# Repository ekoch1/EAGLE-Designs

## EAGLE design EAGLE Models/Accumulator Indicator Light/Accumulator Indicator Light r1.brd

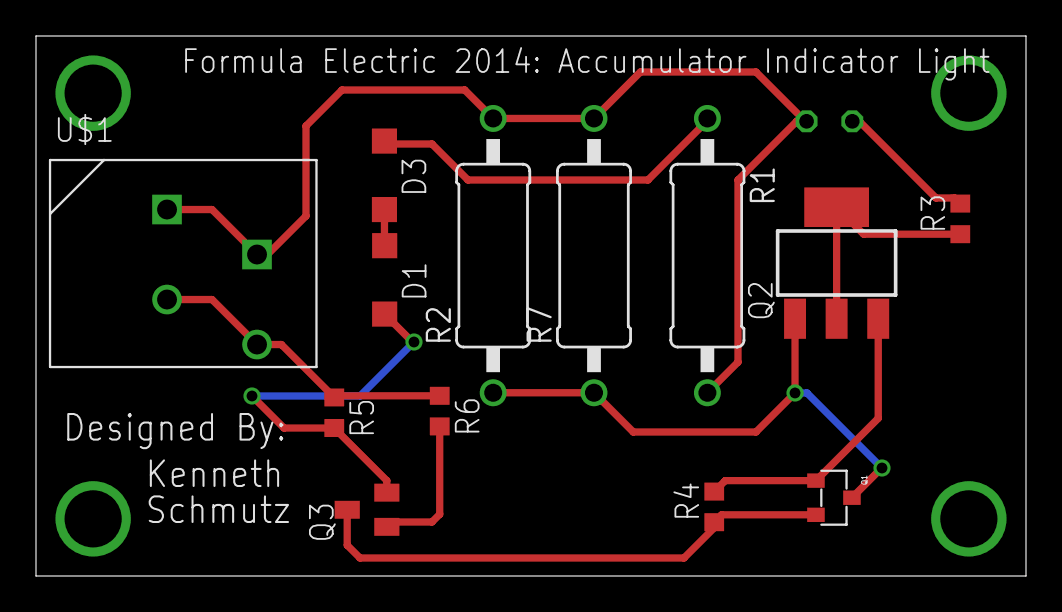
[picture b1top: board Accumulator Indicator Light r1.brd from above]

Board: 2 copper layers, 55.0 x 30.0 mm, 14 parts (1 on the bottom side), 11 nets.

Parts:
D1: DFLZ33; SOD123
D3: BZT52C6V2-7-F; SOD123
LED1: TLLG4400; LED3MM
Q1: MMBT4401-7-F; SOT-23-3
Q2: FZT857; SOT223
Q3: FZT849; SOT23
R1: 100k; 0411/15
R2, R7: 60k; 0411/15
R3: 1k; R0603
R4: 47; R0603
R5: 100k; R0603
R6: 100; R0603
U$1: CONN_2; CONNECTOR_2

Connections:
0: R5.1, R6.1, U$1.3, U$1.4
B1: D1.A, Q3.2, R5.2
B2: Q1.P$1, Q2.1, R2.1, R7.1
C1: Q1.P$3, Q3.3, R4.1
C2: Q2.2, Q2.4, R3.1
E1: Q3.1, R6.2
E2: Q1.P$2, Q2.3, R4.2
unnamed: D1.C, D3.A
unnamed: LED1.K, R3.2
unnamed: LED1.A, R1.2, R2.2, R7.2, U$1.1, U$1.2
R1: D3.C, R1.1

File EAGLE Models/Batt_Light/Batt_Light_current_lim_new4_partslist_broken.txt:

Partlist	exported	from	C:/Users/Kenny	Schmutz/Dropbox/Formula	Electric/Electrical/Models/EAGLE	Models/Batt_Light/Batt_Light_1/Batt_Light_current_lim_new4.sch	at	4/5/2014	4:37:56	PM								
																		
ordered?	Value	Device	Package	Parts	Description	MF	OC_FARNELL	SPICETYPE	SPICE_DESCRIPTION									
yes	100	R-US_R0603	R0603	R6	"RESISTOR,"	American	symbol											
yes	100k	R-US_0411/15	0411/15	R1	"RESISTOR,"	American	symbol											
yes	100k	R-US_R0603	R0603	R5	"RESISTOR,"	American	symbol											
yes	1k	R-US_R0603	R0603	R3	"RESISTOR,"	American	symbol											
have already	2N5210	2N5210	TO92D	Q1	NPN	TRANSISTOR												
yes	30k	R-US_0411/15	0411/15	R2	"RESISTOR,"	American	symbol											
yes	47	R-US_R0603	R0603	R4	"RESISTOR,"	American	symbol											
yes	BZT52C6V2-7-F	ZENER	SOD123	D3	Zener	Diode	diode	Diode										
	CONN_2	CONN_2	CONNECTOR_2	U$1														
yes	DFLZ33	ZENER	SOD123	D1	Zener	Diode	diode	Diode										
	FZT849	NPN	SOT23	Q3	Bipolar	NPN	transistor											
	FZT857	FZT857	SOT223	Q2	FZT857CT-ND													
	TLLG4400	TLLG4400	LED3MM	LED1	Low	Current	(2mA)	LED	3	mm	Tinted	Diffused	Package	color	GREEN	VISHAY	SEMICONDUCTOR	1612435

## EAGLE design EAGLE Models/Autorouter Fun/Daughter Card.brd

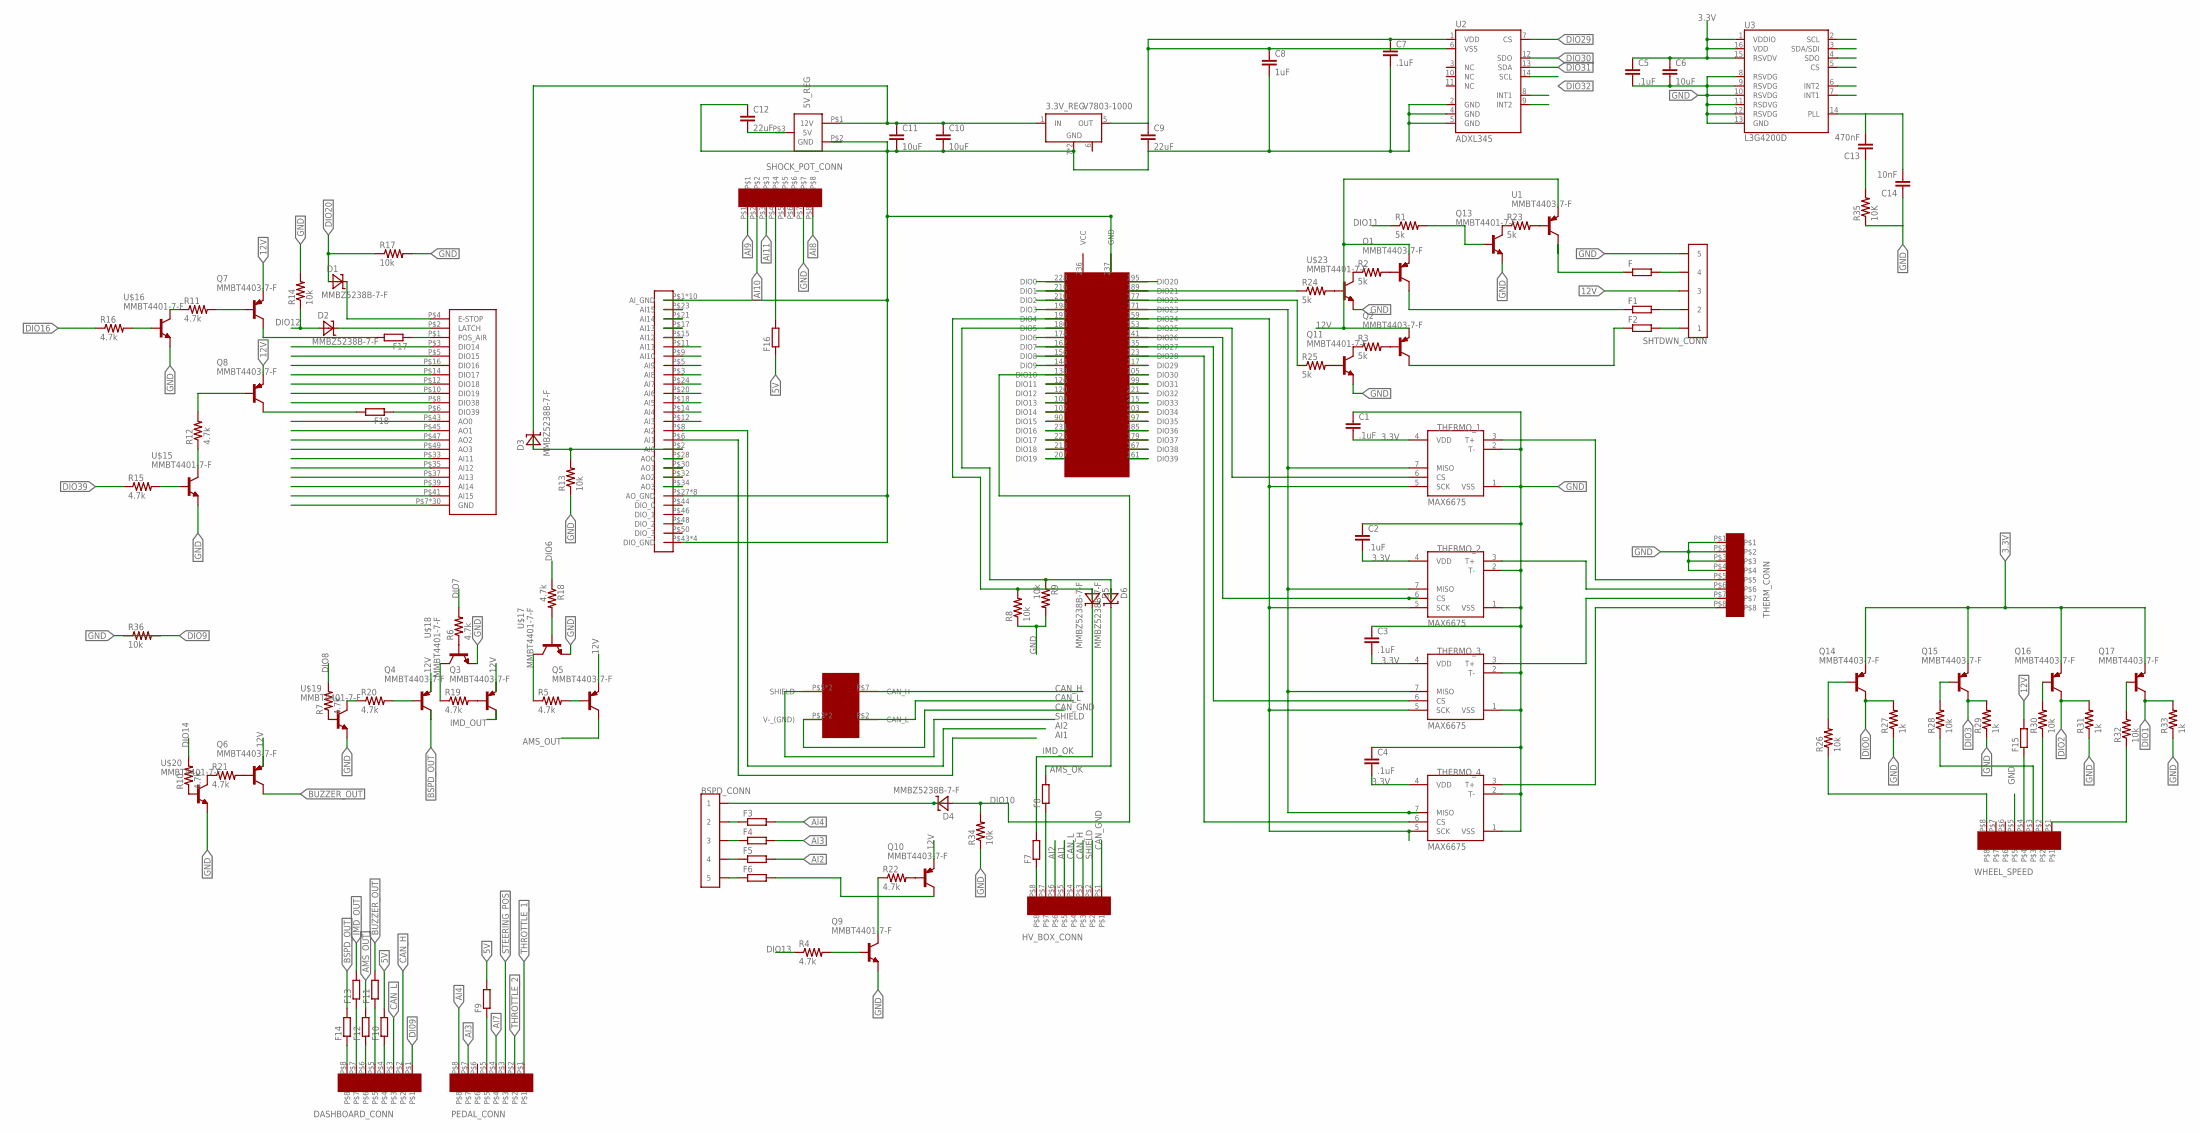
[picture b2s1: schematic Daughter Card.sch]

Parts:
3.3V_REG: V7803-1000; V78XX-1000
5V_REG: V78XX-1500; V78XX-1500R
BSPD_CONN: CONN_5; CONNECTOR_5
C1, C2, C3, C4, C5, C7: .1uF; 0603-CAP
C6, C10, C11: 10uF; 0603-CAP
C8: 1uF; 0603-CAP
C9, C12: 22uF; 0603-CAP
C13: 470nF; 0603-CAP
C14: 10nF; 0603-CAP
D1, D2, D3, D4, D5, D6: MMBZ5238B-7-F; SOT-23-3
DASHBOARD_CONN: EN3_PCB_8
F, F1, F2, F3, F4, F5, F6, F7, F8, F9, F10, F11, F12, F13, F14, F15, F16, F17, F18: R-EU_R0402; R0402
HV_BOX_CONN: EN3_PCB_8
PEDAL_CONN: EN3_PCB_8
Q1, Q2, Q3, Q4, Q5, Q6, Q7, Q8, Q10, Q14, Q15, Q16, Q17: MMBT4403-7-F; SOT-23-3
Q9, Q11, Q13: MMBT4401-7-F; SOT-23-3
R1, R2, R3, R23, R24, R25: 5k; R0402
R4, R5, R6, R7, R10, R11, R12, R15, R16, R18, R19, R20, R21, R22: 4.7k; R0402
R8, R9, R13, R14, R17, R26, R28, R30, R32, R34, R36: 10k; R0402
R27, R29, R31, R33: 1k; R0402
R35: 10K; 0603-RES
SBRIO_ANALOG: SBRIO_MIO; SBRIO_J502_J503
SBRIO_AUX: SBRIO_AUX; SBRIO_J502_J503
SHOCK_POT_CONN: EN3_PCB_8
SHTDWN_CONN: CONN_5; CONNECTOR_5
THERMO_1, THERMO_2, THERMO_3, THERMO_4: MAX6675; SO08
THERM_CONN: EN3_PCB_8
U1: MMBT4403-7-F; SOT-23-3
U2: ADXL345; LGA14
U3: L3G4200D; LGA16-4X4
U$2: SBRIO_W500; SBRIO_W
U$3: SBRIO_RMC; SEAM-40-XX.X-XX-06-X-A
U$15, U$16, U$17, U$18, U$19, U$20, U$23: MMBT4401-7-F; SOT-23-3
WHEEL_SPEED: EN3_PCB_8

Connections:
3.3V: 3.3V_REG.5 (OUT), C1.2, C2.2, C3.2, C4.2, C5.1, C6.1, C7.1, C8.1, C9.1, Q14.P$3 (E), Q15.P$3 (E), Q16.P$3 (E), Q17.P$3 (E), THERMO_1.4 (VDD), THERMO_2.4 (VDD), THERMO_3.4 (VDD), THERMO_4.4 (VDD), U2.1 (VDD), U2.6 (VSS), U3.1 (VDDIO), U3.15 (RSVDV), U3.16 (VDD)
5V: 5V_REG.P$3 (5V), C12.2, F9.2, F10.2, F16.1
12V: 3.3V_REG.1 (IN), 5V_REG.P$1 (12V), C10.1, C11.1, D3.P$1 (C), F15.2, Q1.P$3 (E), Q2.P$3 (E), Q3.P$3 (E), Q4.P$3 (E), Q5.P$3 (E), Q6.P$3 (E), Q7.P$3 (E), Q8.P$3 (E), Q10.P$3 (E), SHTDWN_CONN.5 (3), SHTDWN_CONN.6 (3), U1.P$3 (E)
AI1: HV_BOX_CONN.P$5, SBRIO_ANALOG.P$6 (AI1)
AI2: F5.2, HV_BOX_CONN.P$6, SBRIO_ANALOG.P$8 (AI2)
AI3: F4.2, PEDAL_CONN.P$7, SBRIO_ANALOG.P$12 (AI3)
AI4: F3.2, PEDAL_CONN.P$8, SBRIO_ANALOG.P$14 (AI4)
AI7: PEDAL_CONN.P$4, SBRIO_ANALOG.P$24 (AI7)
AI8: SBRIO_ANALOG.P$3 (AI8), SHOCK_POT_CONN.P$8
AI9: SBRIO_ANALOG.P$5 (AI9), SHOCK_POT_CONN.P$1
AI10: SBRIO_ANALOG.P$9 (AI10), SHOCK_POT_CONN.P$2
AI11: SBRIO_ANALOG.P$11 (AI11), SBRIO_AUX.P$33 (AI11), SHOCK_POT_CONN.P$3
AI12: SBRIO_ANALOG.P$15 (AI12), SBRIO_AUX.P$35 (AI12)
AI13: SBRIO_ANALOG.P$17 (AI13), SBRIO_AUX.P$37 (AI13)
AI15: SBRIO_ANALOG.P$23 (AI15), SBRIO_AUX.P$41 (AI15)
AMS_OK: D6.P$1 (C), F8.2
AMS_OUT: F12.2, Q5.P$1 (C)
AO0: SBRIO_ANALOG.P$28 (AO0), SBRIO_AUX.P$43 (AO0)
AO1: SBRIO_ANALOG.P$30 (AO1), SBRIO_AUX.P$45 (AO1)
AO2: SBRIO_ANALOG.P$32 (AO2), SBRIO_AUX.P$47 (AO2)
AO3: SBRIO_ANALOG.P$34 (AO3), SBRIO_AUX.P$49 (AO3)
BSPD_OUT: F14.2, Q4.P$1 (C)
BUZZER_OUT: F11.2, Q6.P$1 (C)
CAN_GND: HV_BOX_CONN.P$1, U$2.P$3 (V-_(GND)), U$2.P$6 (V-_(GND))
CAN_H: DASHBOARD_CONN.P$2, HV_BOX_CONN.P$3, U$2.P$7 (CAN_H)
CAN_L: DASHBOARD_CONN.P$3, HV_BOX_CONN.P$4, U$2.P$2 (CAN_L)
DI09: DASHBOARD_CONN.P$1
DIO0: Q14.P$1 (C), R27.2, U$3.228 (DIO0)
DIO1: Q17.P$1 (C), R33.2, U$3.216 (DIO1)
DIO2: Q16.P$1 (C), R31.2, U$3.210 (DIO2)
DIO3: Q15.P$1 (C), R29.2, U$3.198 (DIO3)
DIO6: R18.1, U$3.174 (DIO6)
DIO7: R6.2, U$3.162 (DIO7)
DIO8: R7.2, U$3.156 (DIO8)
DIO9: R36.2, U$3.144 (DIO9)
DIO10: D4.P$2 (A), R34.2, U$3.138 (DIO10)
DIO11: R1.1, U$3.126 (DIO11)
DIO12: D2.P$2 (A), R14.1, U$3.120 (DIO12)
DIO13: R4.1, U$3.108 (DIO13)
DIO14: R10.2, SBRIO_AUX.P$3 (DIO14), U$3.102 (DIO14)
DIO15: SBRIO_AUX.P$5 (DIO15), U$3.90 (DIO15)
DIO16: R16.1, SBRIO_AUX.P$16 (DIO16), U$3.231 (DIO16)
DIO17: SBRIO_AUX.P$14 (DIO17), U$3.225 (DIO17)
DIO18: SBRIO_AUX.P$12 (DIO18), U$3.213 (DIO18)
DIO19: SBRIO_AUX.P$10 (DIO19), U$3.207 (DIO19)
DIO20: D1.P$2 (A), R17.1, U$3.195 (DIO20)
DIO29: U2.7 (CS), U$3.117 (DIO29)
DIO30: U2.12 (SDO), U3.4 (SDO), U$3.105 (DIO30)
DIO31: U2.13 (SDA), U3.3 (SDA/SDI), U$3.99 (DIO31)
DIO32: U2.14 (SCL), U3.2 (SCL), U$3.221 (DIO32)
DIO33: U3.5 (CS), U$3.215 (DIO33)
DIO34: U3.7 (INT1), U$3.203 (DIO34)
DIO35: U3.6 (INT2), U$3.197 (DIO35)
DIO36: U2.8 (INT1), U$3.185 (DIO36)
DIO37: U2.9 (INT2), U$3.179 (DIO37)
DIO38: SBRIO_AUX.P$8 (DIO38), U$3.167 (DIO38)
DIO39: R15.1, U$3.161 (DIO39)
GND: 3.3V_REG.7 (GND), 3.3V_REG.9 (GND), 5V_REG.P$2 (GND), C1.1, C2.1, C3.1, C4.1, C5.2, C6.2, C7.2, C8.2, C9.2, C10.2, C11.2, C12.1, C14.1, Q9.P$3 (E), Q11.P$3 (E), Q13.P$3 (E), R8.1, R9.2, R13.1, R14.2, R17.2, R27.1, R29.1, R31.1, R33.1, R34.1, R35.1, R36.1, SBRIO_ANALOG.P$1 (AI_GND), SBRIO_ANALOG.P$4 (AI_GND), SBRIO_ANALOG.P$7 (AI_GND), SBRIO_ANALOG.P$10 (AI_GND), SBRIO_ANALOG.P$13 (AI_GND), SBRIO_ANALOG.P$16 (AI_GND), SBRIO_ANALOG.P$19 (AI_GND), SBRIO_ANALOG.P$22 (AI_GND), SBRIO_ANALOG.P$25 (AI_GND), SBRIO_ANALOG.P$26 (AI_GND), SBRIO_ANALOG.P$27 (AO_GND), SBRIO_ANALOG.P$29 (AO_GND), SBRIO_ANALOG.P$31 (AO_GND), SBRIO_ANALOG.P$33 (AO_GND), SBRIO_ANALOG.P$35 (AO_GND), SBRIO_ANALOG.P$37 (AO_GND), SBRIO_ANALOG.P$39 (AO_GND), SBRIO_ANALOG.P$41 (AO_GND), SBRIO_ANALOG.P$43 (DIO_GND), SBRIO_ANALOG.P$45 (DIO_GND), SBRIO_ANALOG.P$47 (DIO_GND), SBRIO_ANALOG.P$49 (DIO_GND), SBRIO_AUX.P$7 (GND), SBRIO_AUX.P$9 (GND), SBRIO_AUX.P$11 (GND), SBRIO_AUX.P$13 (GND), SBRIO_AUX.P$15 (GND), SBRIO_AUX.P$17 (GND), SBRIO_AUX.P$18 (GND), SBRIO_AUX.P$19 (GND), SBRIO_AUX.P$20 (GND), SBRIO_AUX.P$21 (GND), SBRIO_AUX.P$22 (GND), SBRIO_AUX.P$23 (GND), SBRIO_AUX.P$24 (GND), SBRIO_AUX.P$25 (GND), SBRIO_AUX.P$26 (GND), SBRIO_AUX.P$27 (GND), SBRIO_AUX.P$28 (GND), SBRIO_AUX.P$29 (GND), SBRIO_AUX.P$30 (GND), SBRIO_AUX.P$31 (GND), SBRIO_AUX.P$32 (GND), SBRIO_AUX.P$34 (GND), SBRIO_AUX.P$36 (GND), SBRIO_AUX.P$38 (GND), SBRIO_AUX.P$40 (GND), SBRIO_AUX.P$42 (GND), SBRIO_AUX.P$44 (GND), SBRIO_AUX.P$46 (GND), SBRIO_AUX.P$48 (GND), SBRIO_AUX.P$50 (GND), SHOCK_POT_CONN.P$7, SHTDWN_CONN.9 (5), SHTDWN_CONN.10 (5), THERMO_1.1 (VSS), THERMO_1.2 (T-), THERMO_2.1 (VSS), THERMO_2.2 (T-), THERMO_3.1 (VSS), THERMO_3.2 (T-), THERMO_4.1 (VSS), THERMO_4.2 (T-), THERM_CONN.P$1, THERM_CONN.P$2, THERM_CONN.P$3, THERM_CONN.P$4, U2.2 (GND), U2.4 (GND), U2.5 (GND), U3.8 (RSVDG), U3.9 (RSVDG), U3.10 (RSVDG), U3.11 (RSDVG), U3.12 (RSVDG), U3.13 (GND), U$3.237 (GND), U$15.P$3 (E), U$16.P$3 (E), U$17.P$3 (E), U$18.P$3 (E), U$19.P$3 (E), U$20.P$3 (E), U$23.P$3 (E), WHEEL_SPEED.P$5
IMD_OK: D5.P$1 (C), F7.2
IMD_OUT: F13.2, Q3.P$1 (C)
unnamed: D2.P$1 (C), SBRIO_AUX.P$2 (LATCH)
unnamed: D1.P$1 (C), SBRIO_AUX.P$4 (E-STOP)
unnamed: R32.1, WHEEL_SPEED.P$1
unnamed: D3.P$2 (A), R13.2, SBRIO_ANALOG.P$2 (AI0)
unnamed: Q6.P$2 (B), R21.2
unnamed: Q16.P$2 (B), R30.2
unnamed: F1.1, Q1.P$1 (C)
unnamed: F2.1, Q2.P$1 (C)
unnamed: R28.1, WHEEL_SPEED.P$3
unnamed: R26.1, WHEEL_SPEED.P$8
unnamed: R24.1, U$3.189 (DIO21)
unnamed: R25.1, U$3.177 (DIO22)
unnamed: F8.1, HV_BOX_CONN.P$7
unnamed: F7.1, HV_BOX_CONN.P$8
unnamed: D5.P$2 (A), R8.2, U$3.192 (DIO4)
unnamed: D6.P$2 (A), R9.1, U$3.180 (DIO5)
unnamed: THERMO_1.7 (MISO), THERMO_2.7 (MISO), THERMO_3.7 (MISO), THERMO_4.7 (MISO), U$3.171 (DIO23)
unnamed: THERMO_1.5 (SCK), THERMO_2.5 (SCK), THERMO_3.5 (SCK), THERMO_4.5 (SCK), U$3.159 (DIO24)
unnamed: F16.2, SHOCK_POT_CONN.P$4
unnamed: F15.1, WHEEL_SPEED.P$4
unnamed: F9.1, PEDAL_CONN.P$5
unnamed: DASHBOARD_CONN.P$4, F10.1
unnamed: DASHBOARD_CONN.P$5, F11.1
unnamed: THERMO_1.6 (CS), U$3.153 (DIO25)
unnamed: THERMO_2.6 (CS), U$3.141 (DIO26)
unnamed: THERMO_3.6 (CS), U$3.135 (DIO27)
unnamed: THERMO_4.6 (CS), U$3.123 (DIO28)
unnamed: THERMO_1.3 (T+), THERM_CONN.P$5
unnamed: THERMO_2.3 (T+), THERM_CONN.P$6
unnamed: THERMO_3.3 (T+), THERM_CONN.P$7
unnamed: THERMO_4.3 (T+), THERM_CONN.P$8
unnamed: DASHBOARD_CONN.P$6, F12.1
unnamed: DASHBOARD_CONN.P$7, F13.1
unnamed: DASHBOARD_CONN.P$8, F14.1
unnamed: F.2, SHTDWN_CONN.7 (4), SHTDWN_CONN.8 (4)
unnamed: C13.2, C14.2, U3.14 (PLL)
unnamed: C13.1, R35.2
unnamed: F1.2, SHTDWN_CONN.3 (2), SHTDWN_CONN.4 (2)
unnamed: F2.2, SHTDWN_CONN.1, SHTDWN_CONN.2 (1)
unnamed: BSPD_CONN.9 (5), BSPD_CONN.10 (5), F6.1
unnamed: BSPD_CONN.1, BSPD_CONN.2 (1), D4.P$1 (C)
unnamed: BSPD_CONN.7 (4), BSPD_CONN.8 (4), F5.1
unnamed: F.1, U1.P$1 (C)
unnamed: F6.2, Q10.P$1 (C)
unnamed: R23.2, U1.P$2 (B)
unnamed: Q1.P$2 (B), R2.2
unnamed: Q2.P$2 (B), R3.2
unnamed: Q10.P$2 (B), R22.2
unnamed: Q5.P$2 (B), R5.2
unnamed: Q3.P$2 (B), R19.2
unnamed: BSPD_CONN.5 (3), BSPD_CONN.6 (3), F4.1
unnamed: BSPD_CONN.3 (2), BSPD_CONN.4 (2), F3.1
unnamed: Q7.P$2 (B), R11.2
unnamed: F17.1, SBRIO_AUX.P$1 (POS_AIR)
unnamed: F17.2, Q7.P$1 (C)
unnamed: F18.2, Q8.P$1 (C)
unnamed: Q8.P$2 (B), R12.2
unnamed: F18.1, SBRIO_AUX.P$6 (DIO39)
unnamed: R15.2, U$15.P$2 (B)
unnamed: R12.1, U$15.P$1 (C)
unnamed: R16.2, U$16.P$2 (B)
unnamed: R11.1, U$16.P$1 (C)
unnamed: R5.1, U$17.P$1 (C)
unnamed: R18.2, U$17.P$2 (B)
unnamed: R19.1, U$18.P$1 (C)
unnamed: R6.1, U$18.P$2 (B)
unnamed: Q4.P$2 (B), R20.2
unnamed: R20.1, U$19.P$1 (C)
unnamed: R7.1, U$19.P$2 (B)
unnamed: R21.1, U$20.P$1 (C)
unnamed: R10.1, U$20.P$2 (B)
unnamed: Q9.P$1 (C), R22.1
unnamed: Q9.P$2 (B), R4.2
unnamed: Q13.P$1 (C), R23.1
unnamed: Q13.P$2 (B), R1.2
unnamed: R2.1, U$23.P$1 (C)
unnamed: Q11.P$1 (C), R3.1
unnamed: R24.2, U$23.P$2 (B)
unnamed: Q11.P$2 (B), R25.2
unnamed: Q14.P$2 (B), R26.2
unnamed: Q15.P$2 (B), R28.2
unnamed: R30.1, WHEEL_SPEED.P$2
unnamed: Q17.P$2 (B), R32.2
SHIELD: HV_BOX_CONN.P$2, U$2.P$5 (SHIELD), U$2.P$10 (SHIELD)
STEERING_POS: PEDAL_CONN.P$3, SBRIO_ANALOG.P$21 (AI14), SBRIO_AUX.P$39 (AI14)
THROTTLE_1: PEDAL_CONN.P$1, SBRIO_ANALOG.P$18 (AI5)
THROTTLE_2: PEDAL_CONN.P$2, SBRIO_ANALOG.P$20 (AI6)
VCC: U$3.236 (VCC)

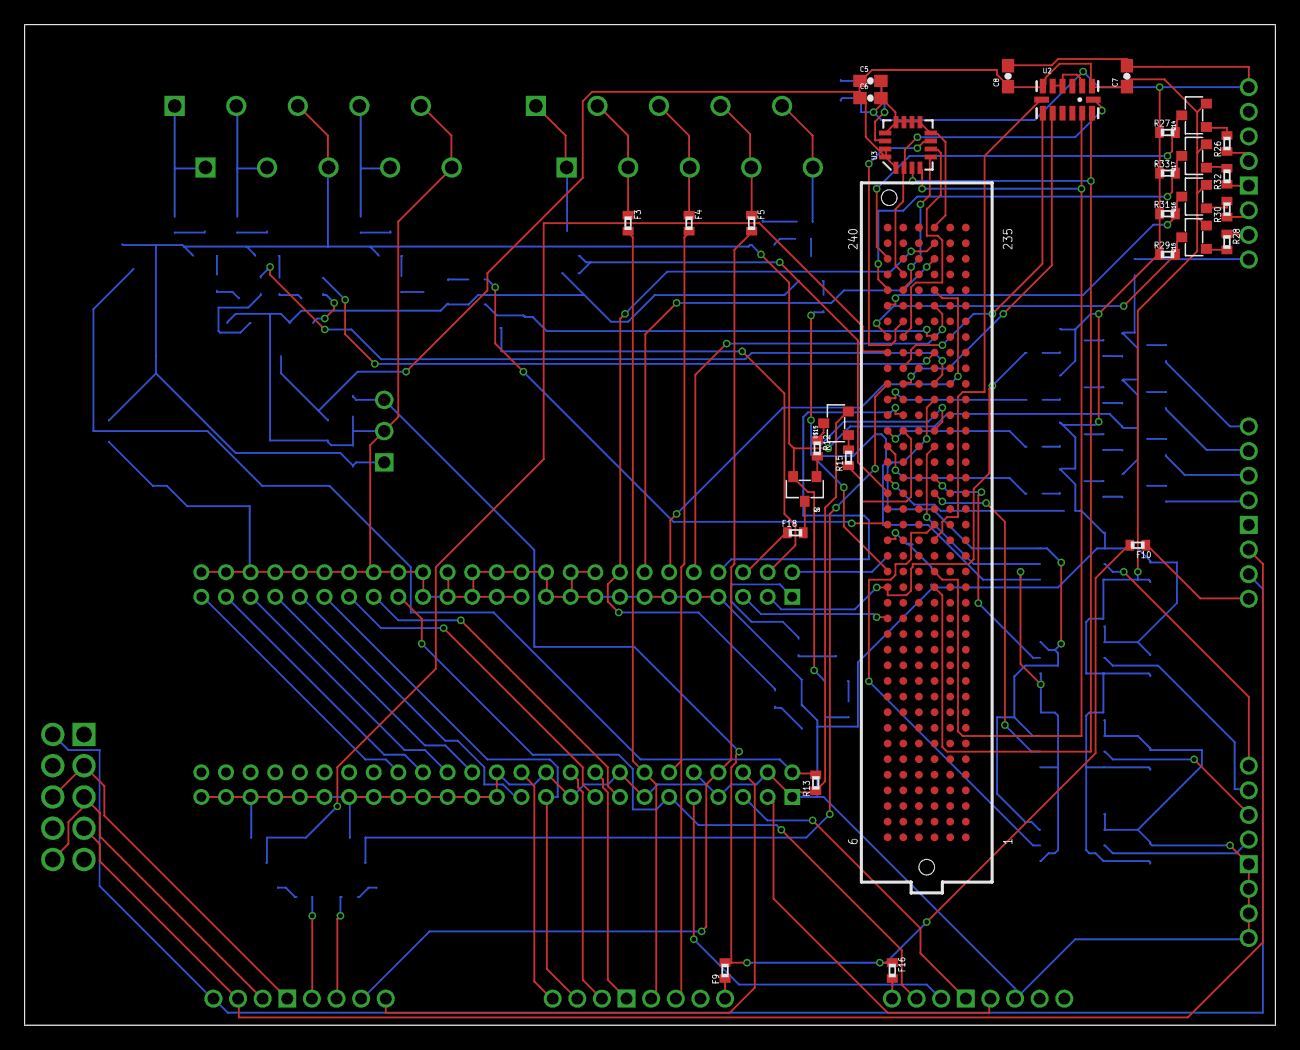
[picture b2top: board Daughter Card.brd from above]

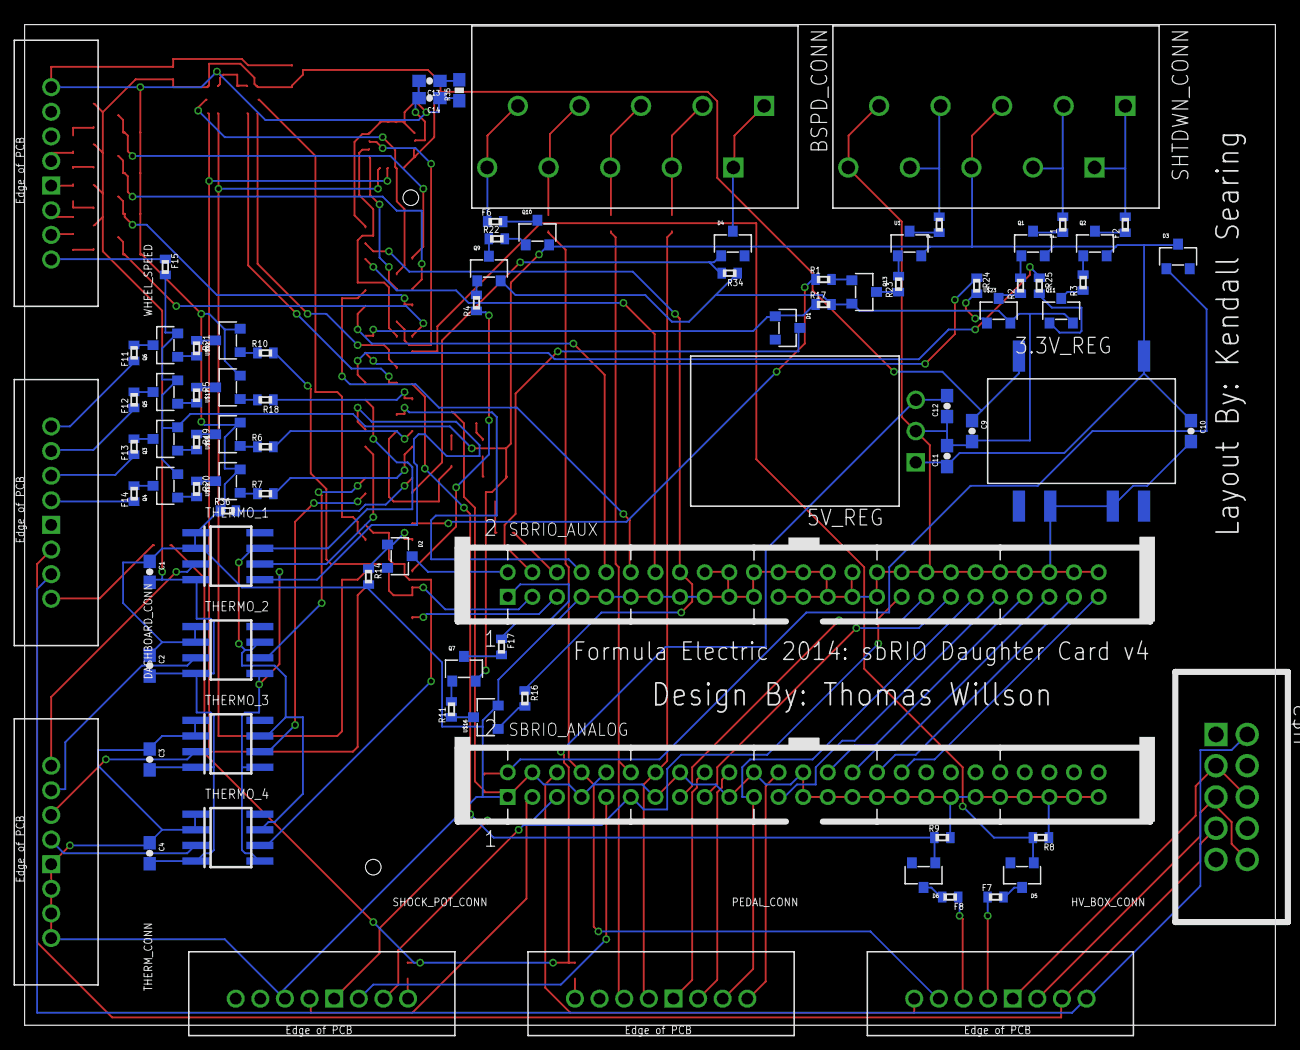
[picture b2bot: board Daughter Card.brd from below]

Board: 2 copper layers, 101.6 x 81.3 mm, 119 parts (88 on the bottom side), 146 nets.

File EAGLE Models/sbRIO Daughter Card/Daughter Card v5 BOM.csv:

"Part";"Value";"Device";"Package";"Description";"MF";"MPN";"OC_FARNELL";"OC_NEWARK";
"3.3V_REG";"V7803-1000";"V7803-1000";"V78XX-1000";"";"";"";"";"";
"5V_REG";"V78XX-1500";"V78XX-1500";"V78XX-1500R";"";"";"";"";"";
"ACCUMULATOR_CONN";"RJ45-6L21-S";"RJ45-6L21-S";"RJ45-SHIELD1";"RJ45 Low Profile Shield Type 2";"";"";"unknown";"unknown";
"AIO_PO_CONN";"2516-5";"2516-5";"PAK100/2500-5-16";"3M (TM) Pak 100 4-Wall Header";"";"D2516-5002-AR";"9838376";"12P7055";
"BSPD_CONN";"CONN_5";"CONN_5";"CONNECTOR_5";"";"";"";"";"";
"C5";".1uF";"CAP0603-CAP";"0603-CAP";"Capacitor";"";"";"";"";
"C6";"10uF";"CAP0603-CAP";"0603-CAP";"Capacitor";"";"";"";"";
"C7";".1uF";"CAP0603-CAP";"0603-CAP";"Capacitor";"";"";"";"";
"C8";"1uF";"CAP0603-CAP";"0603-CAP";"Capacitor";"";"";"";"";
"C9";"22uF";"CAP0603-CAP";"0603-CAP";"Capacitor";"";"";"";"";
"C10";"10uF";"CAP0603-CAP";"0603-CAP";"Capacitor";"";"";"";"";
"C11";"10uF";"CAP0603-CAP";"0603-CAP";"Capacitor";"";"";"";"";
"C12";"22uF";"CAP0603-CAP";"0603-CAP";"Capacitor";"";"";"";"";
"C13";"470nF";"CAP0603-CAP";"0603-CAP";"Capacitor";"";"";"";"";
"C14";"10nF";"CAP0603-CAP";"0603-CAP";"Capacitor";"";"";"";"";
"D1";"MMBZ5238B-7-F";"MMBZ5238B-7-F";"SOT-23-3";"Digikey: MMBZ5238B-FDICT-ND";"";"";"";"";
"D2";"MMBZ5238B-7-F";"MMBZ5238B-7-F";"SOT-23-3";"Digikey: MMBZ5238B-FDICT-ND";"";"";"";"";
"D3";"MMBZ5238B-7-F";"MMBZ5238B-7-F";"SOT-23-3";"Digikey: MMBZ5238B-FDICT-ND";"";"";"";"";
"D4";"MMBZ5238B-7-F";"MMBZ5238B-7-F";"SOT-23-3";"Digikey: MMBZ5238B-FDICT-ND";"";"";"";"";
"D5";"MMBZ5238B-7-F";"MMBZ5238B-7-F";"SOT-23-3";"Digikey: MMBZ5238B-FDICT-ND";"";"";"";"";
"D6";"MMBZ5238B-7-F";"MMBZ5238B-7-F";"SOT-23-3";"Digikey: MMBZ5238B-FDICT-ND";"";"";"";"";
"F1";"";"R-EU_R0402";"R0402";"RESISTOR, European symbol";"";"";"";"";
"F2";"";"R-EU_R0402";"R0402";"RESISTOR, European symbol";"";"";"";"";
"F3";"";"R-EU_R0402";"R0402";"RESISTOR, European symbol";"";"";"";"";
"F4";"";"R-EU_R0402";"R0402";"RESISTOR, European symbol";"";"";"";"";
"F5";"";"R-EU_R0402";"R0402";"RESISTOR, European symbol";"";"";"";"";
"F6";"";"R-EU_R0402";"R0402";"RESISTOR, European symbol";"";"";"";"";
"F7";"";"R-EU_R0402";"R0402";"RESISTOR, European symbol";"";"";"";"";
"F8";"";"R-EU_R0402";"R0402";"RESISTOR, European symbol";"";"";"";"";
"F9";"";"R-EU_R0402";"R0402";"RESISTOR, European symbol";"";"";"";"";
"F10";"";"R-EU_R0402";"R0402";"RESISTOR, European symbol";"";"";"";"";
"F14";"";"R-EU_R0402";"R0402";"RESISTOR, European symbol";"";"";"";"";
"F15";"";"R-EU_R0402";"R0402";"RESISTOR, European symbol";"";"";"";"";
"F16";"";"R-EU_R0402";"R0402";"RESISTOR, European symbol";"";"";"";"";
"F17";"";"R-EU_R0402";"R0402";"RESISTOR, European symbol";"";"";"";"";
"F18";"";"R-EU_R0402";"R0402";"RESISTOR, European symbol";"";"";"";"";
"F19";"";"R-EU_R0402";"R0402";"RESISTOR, European symbol";"";"";"";"";
"F20";"";"R-EU_R0402";"R0402";"RESISTOR, European symbol";"";"";"";"";
"F21";"";"R-EU_R0402";"R0402";"RESISTOR, European symbol";"";"";"";"";
"F22";"";"R-EU_R0402";"R0402";"RESISTOR, European symbol";"";"";"";"";
"IC1";"BTS716G";"BTS716G";"PG-DSO-20";"Smart High-Side Power Switch Four Channels: 4 x 140mOhm staus Feedback";"";"";"unknown";"unknown";
"IC2";"BTS716G";"BTS716G";"PG-DSO-20";"Smart High-Side Power Switch Four Channels: 4 x 140mOhm staus Feedback";"";"";"unknown";"unknown";
"IC3";"BTS716G";"BTS716G";"PG-DSO-20";"Smart High-Side Power Switch Four Channels: 4 x 140mOhm staus Feedback";"";"";"unknown";"unknown";
"Q7";"MMBT4403-7-F";"MMBT4403-7-F";"SOT-23-3";"";"";"";"";"";
"Q8";"MMBT4403-7-F";"MMBT4403-7-F";"SOT-23-3";"";"";"";"";"";
"R8";"10k";"R-US_R0402";"R0402";"RESISTOR, American symbol";"";"";"";"";
"R9";"10k";"R-US_R0402";"R0402";"RESISTOR, American symbol";"";"";"";"";
"R11";"4.7k";"R-US_R0402";"R0402";"RESISTOR, American symbol";"";"";"";"";
"R12";"4.7k";"R-US_R0402";"R0402";"RESISTOR, American symbol";"";"";"";"";
"R13";"10k";"R-US_R0402";"R0402";"RESISTOR, American symbol";"";"";"";"";
"R14";"10k";"R-US_R0402";"R0402";"RESISTOR, American symbol";"";"";"";"";
"R15";"4.7k";"R-US_R0402";"R0402";"RESISTOR, American symbol";"";"";"";"";
"R16";"4.7k";"R-US_R0402";"R0402";"RESISTOR, American symbol";"";"";"";"";
"R17";"10k";"R-US_R0402";"R0402";"RESISTOR, American symbol";"";"";"";"";
"R34";"10k";"R-US_R0402";"R0402";"RESISTOR, American symbol";"";"";"";"";
"R35";"10K";"RESISTOR0603-RES";"0603-RES";"Resistor";"";"";"";"";
"R36";"10k";"R-US_R0402";"R0402";"RESISTOR, American symbol";"";"";"";"";
"SBRIO_ANALOG";"SBRIO_MIO";"SBRIO_MIO";"SBRIO_J502_J503";"";"";"";"";"";
"SBRIO_AUX";"SBRIO_AUX";"SBRIO_AUX";"SBRIO_J502_J503";"An output for a lot of the extra pins on the sbRIO.";"";"";"";"";
"SHTDWN_CONN";"CONN_5";"CONN_5";"CONNECTOR_5";"";"";"";"";"";
"TUB_CONN";"2516-5";"2516-5";"PAK100/2500-5-16";"3M (TM) Pak 100 4-Wall Header";"";"D2516-5002-AR";"9838376";"12P7055";
"U$2";"SBRIO_W500";"SBRIO_W500";"SBRIO_W";"";"";"";"";"";
"U$3";"SBRIO_RMC";"SBRIO_RMC";"SEAM-40-XX.X-XX-06-X-A";"";"";"";"";"";
"U$15";"MMBT4401-7-F";"MMBT4401-7-F";"SOT-23-3";"";"";"";"";"";
"U$16";"MMBT4401-7-F";"MMBT4401-7-F";"SOT-23-3";"";"";"";"";"";
"U1";"";"TXB0104PWR";"TSSOP14";"4-Bit Bi-Directional Level Shifter";"";"";"";"";
"U2";"ADXL345";"ADXL345";"LGA14";"3-axis SPI/I2C 2/4/8/16g accelerometer";"";"";"";"";
"U3";"L3G4200D";"L3G4200D";"LGA16-4X4";"L3G4200D Three-axis, digital output gyroscope";"";"";"";"";
"X1";"5566-2";"5566-2";"5566-2";"Mini FIT connector 2 pol";"";"";"1822072";"unknown";
"X2";"";"FTOP-4";"FTOP-4";"AMP connector";"";"";"";"";

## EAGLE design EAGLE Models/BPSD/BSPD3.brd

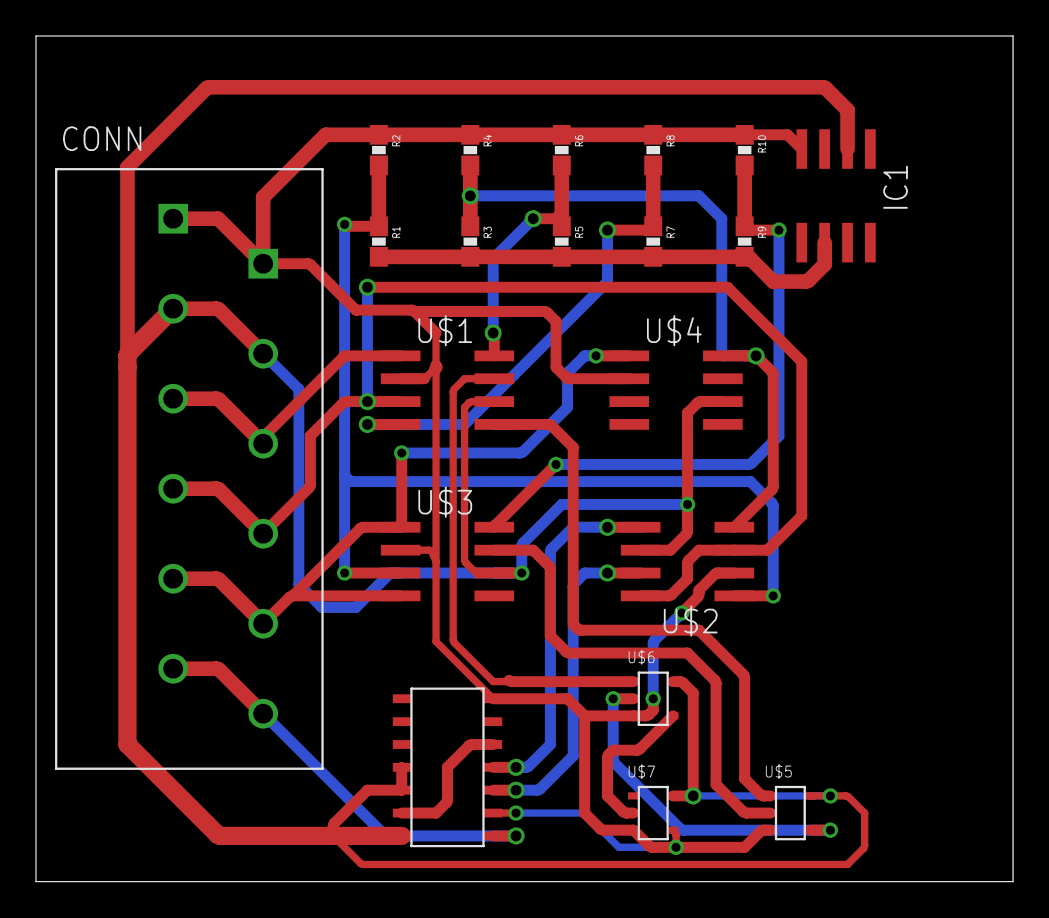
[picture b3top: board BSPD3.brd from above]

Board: 2 copper layers, 54.3 x 47.0 mm, 20 parts (0 on the bottom side), 21 nets.

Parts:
CONN: CONN_6; CONNECTOR_6
IC1: LT1236S-5; SOIC8
R1, R4: 1k; 0603-RES
R2, R3: 9.1k; 0603-RES
R5: 3.3k; 0603-RES
R6: 4.7k; 0603-RES
R7: 8.2k; 0603-RES
R8: 2.2k; 0603-RES
R9: 8.87k; 0603-RES
R10: 1.8k; 0603-RES
U$1, U$2, U$3, U$4: LT1018; SOIC8
U$5: TC4S71FT5LFT-OR_GATE; SSOP5-P-0.95
U$6: TC4S81FT5LFT-AND_GATE; SSOP5-P-0.95
U$7: TC4S69F(TE85L,F); SSOP5-P-0.95
U$8: HEF4082BT,653; NXP_14_SOIC

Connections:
1.06V: R7.1, R8.2, U$1.4
2.95V: R5.1, R6.2, U$1.8
4.5V: R1.1, R2.2, U$2.1, U$3.3
12V: CONN.3, CONN.4, IC1.2, U$1.6, U$2.6, U$3.6, U$4.6, U$5.P$5, U$6.P$5, U$7.P$5, U$8.P$11, U$8.P$12, U$8.P$14
.5V: R3.1, R4.2, U$2.4, U$4.8
.831V: R9.1, R10.2, U$3.8
ALL_OK: CONN.11, CONN.12, U$8.P$1
BF: CONN.7, CONN.8, U$1.3, U$2.3, U$2.8
BR: CONN.9, CONN.10, U$3.1, U$3.4, U$4.1
CURRENT: CONN.5, CONN.6, U$1.1
GND: CONN.1, CONN.2, IC1.4, R2.1, R4.1, R6.1, R8.1, R10.1, U$1.2, U$2.2, U$3.2, U$4.2, U$5.P$3, U$6.P$3, U$7.P$3, U$8.P$7
unnamed: IC1.6, R1.2, R3.2, R5.2, R7.2, R9.2
unnamed: U$1.5, U$5.P$1
unnamed: U$3.7, U$5.P$2
unnamed: U$5.P$4, U$6.P$2
unnamed: U$1.7, U$6.P$1
unnamed: U$6.P$4, U$7.P$2
unnamed: U$7.P$4, U$8.P$2
unnamed: U$2.7, U$8.P$3
unnamed: U$2.5, U$8.P$4
unnamed: U$8.P$5, U$8.P$13

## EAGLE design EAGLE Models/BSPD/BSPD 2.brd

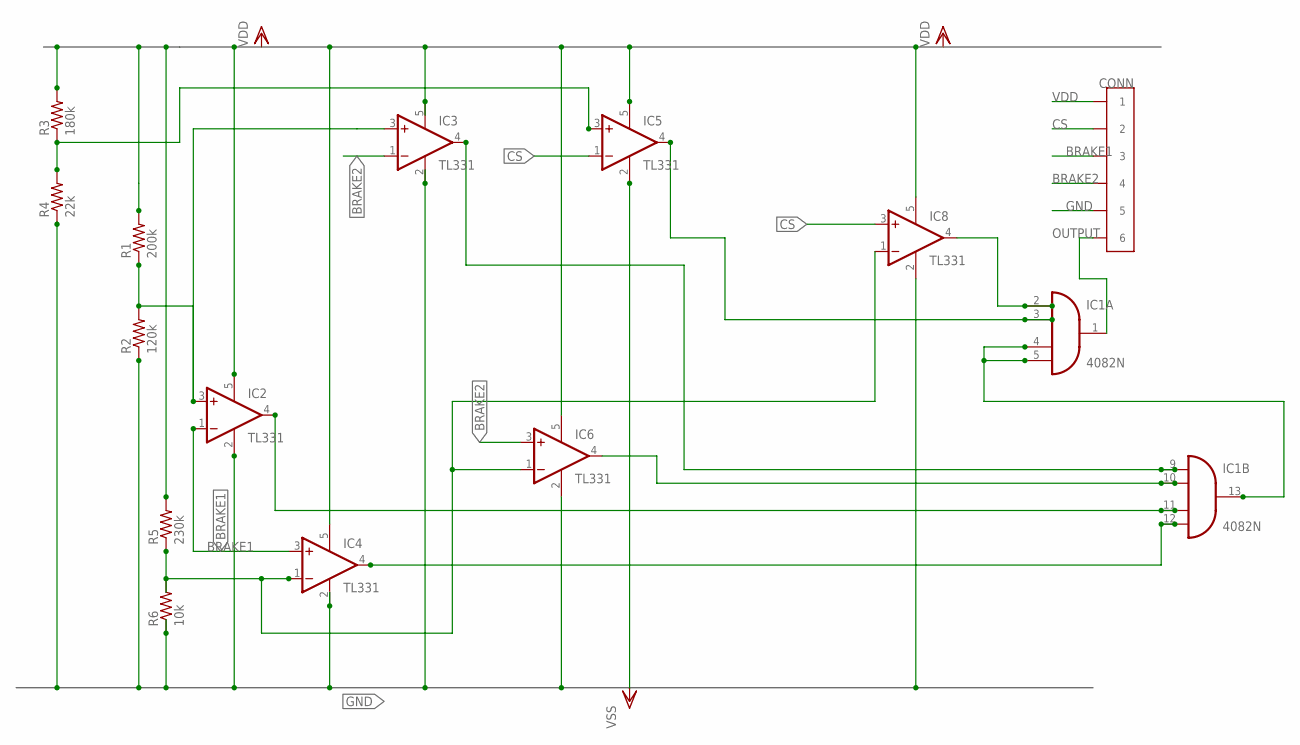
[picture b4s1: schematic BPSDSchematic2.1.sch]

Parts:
CONN: CONN_6; CONNECTOR_6
IC1: 4082N; DIL14
IC2, IC3, IC4, IC5, IC6, IC8: TL331; DBV-R-PDSO-G5
R1: 200k; 0207/15
R2: 120k; 0207/15
R3: 180k; 0207/15
R4: 22k; 0207/15
R5: 230k; 0207/15
R6: 10k; 0207/15

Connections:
BRAKE1: CONN.5 (3), CONN.6 (3), IC2.1 (-IN), IC4.3 (+IN)
BRAKE2: CONN.7 (4), CONN.8 (4), IC3.1 (-IN), IC6.3 (+IN)
CS: CONN.3 (2), CONN.4 (2), IC5.1 (-IN), IC8.3 (+IN)
GND: CONN.9 (5), CONN.10 (5), IC1.7 (VSS), IC2.2 (GND), IC3.2 (GND), IC4.2 (GND), IC5.2 (GND), IC6.2 (GND), IC8.2 (GND), R2.1, R4.1, R6.1
unnamed: IC1.12 (I3), IC4.4 (OUT)
unnamed: IC1.11 (I2), IC2.4 (OUT)
unnamed: IC1.10 (I1), IC6.4 (OUT)
unnamed: IC1.9 (I0), IC3.4 (OUT)
unnamed: IC1.2 (I0), IC8.4 (OUT)
unnamed: IC1.4 (I2), IC1.5 (I3), IC1.13 (O)
unnamed: IC2.3 (+IN), IC3.3 (+IN), R1.1, R2.2
unnamed: IC4.1 (-IN), IC6.1 (-IN), IC8.1 (-IN), R5.1, R6.2
unnamed: IC5.3 (+IN), R3.1, R4.2
unnamed: IC1.3 (I1), IC5.4 (OUT)
VDD: CONN.1, CONN.2 (1), IC1.14 (VDD), IC2.5 (V+), IC3.5 (V+), IC4.5 (V+), IC5.5 (V+), IC6.5 (V+), IC8.5 (V+), R1.2, R3.2, R5.2

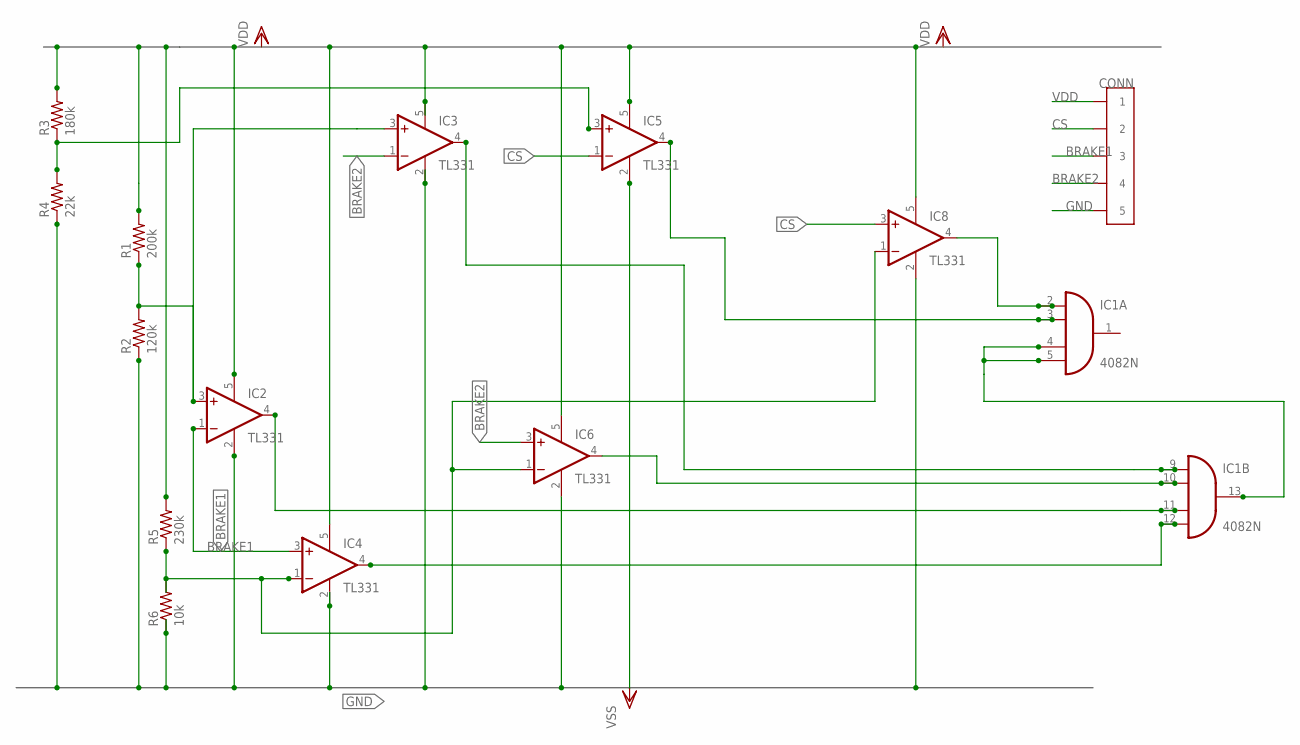
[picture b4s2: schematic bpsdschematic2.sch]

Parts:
CONN: CONN_5; CONNECTOR_5
IC1: 4082N; DIL14
IC2, IC3, IC4, IC5, IC6, IC8: TL331; DBV-R-PDSO-G5
R1: 200k; 0207/15
R2: 120k; 0207/15
R3: 180k; 0207/15
R4: 22k; 0207/15
R5: 230k; 0207/15
R6: 10k; 0207/15

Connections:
BRAKE1: CONN.5 (3), CONN.6 (3), IC2.1 (-IN), IC4.3 (+IN)
BRAKE2: CONN.7 (4), CONN.8 (4), IC3.1 (-IN), IC6.3 (+IN)
CS: CONN.3 (2), CONN.4 (2), IC5.1 (-IN), IC8.3 (+IN)
GND: CONN.9 (5), CONN.10 (5), IC1.7 (VSS), IC2.2 (GND), IC3.2 (GND), IC4.2 (GND), IC5.2 (GND), IC6.2 (GND), IC8.2 (GND), R2.1, R4.1, R6.1
unnamed: IC1.12 (I3), IC4.4 (OUT)
unnamed: IC1.11 (I2), IC2.4 (OUT)
unnamed: IC1.10 (I1), IC6.4 (OUT)
unnamed: IC1.9 (I0), IC3.4 (OUT)
unnamed: IC1.2 (I0), IC8.4 (OUT)
unnamed: IC1.4 (I2), IC1.5 (I3), IC1.13 (O)
unnamed: IC2.3 (+IN), IC3.3 (+IN), R1.1, R2.2
unnamed: IC4.1 (-IN), IC6.1 (-IN), IC8.1 (-IN), R5.1, R6.2
unnamed: IC5.3 (+IN), R3.1, R4.2
unnamed: IC1.3 (I1), IC5.4 (OUT)
VDD: CONN.1, CONN.2 (1), IC1.14 (VDD), IC2.5 (V+), IC3.5 (V+), IC4.5 (V+), IC5.5 (V+), IC6.5 (V+), IC8.5 (V+), R1.2, R3.2, R5.2

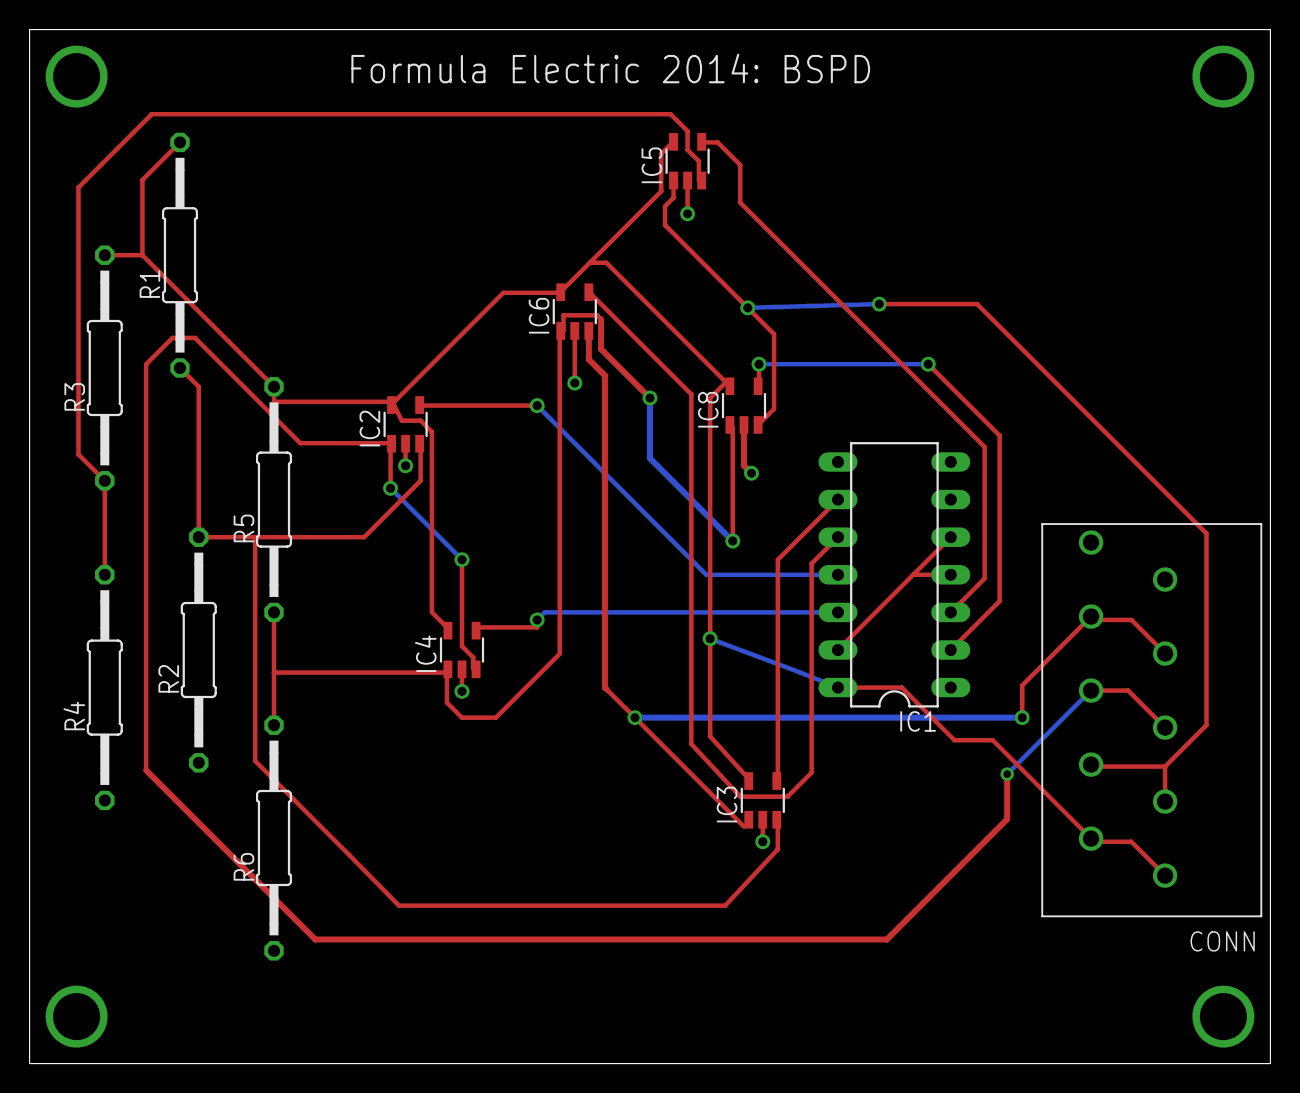
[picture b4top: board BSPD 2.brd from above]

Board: 2 copper layers, 83.8 x 69.8 mm, 14 parts (0 on the bottom side), 15 nets.

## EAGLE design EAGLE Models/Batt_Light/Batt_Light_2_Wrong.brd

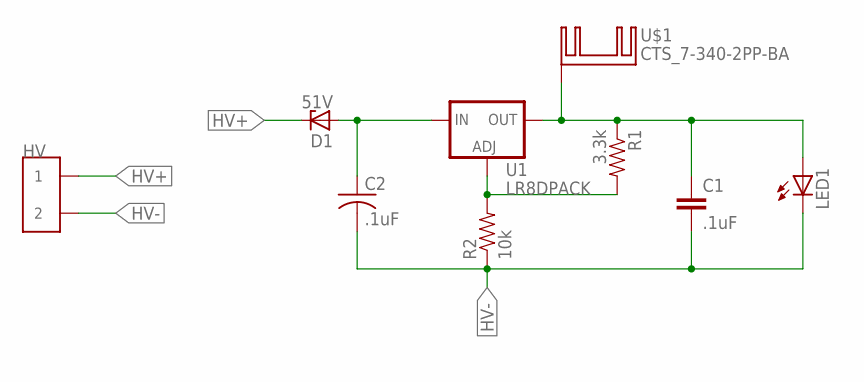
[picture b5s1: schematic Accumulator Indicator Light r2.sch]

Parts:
C1: .1uF; 0603-CAP
C2: .1uF; C2220
D1: 51V; SOT23
HV: CONN_2; CONNECTOR_2
LED1: LEDSMT1206; 1206
R1: 3.3k; 0603-RES
R2: 10k; 0603-RES
U1: LR8DPACK; DPACK
U$1: CTS_7-340-2PP-BA; TO-200_DUAL

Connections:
HV+: D1.3 (C), HV.1, HV.2 (1)
HV-: C1.2, C2.2, HV.3 (2), HV.4 (2), LED1.C, R2.1
N$: C2.1, D1.1 (A), U1.1 (IN)
unnamed: R1.2, R2.2, U1.3 (ADJ)
unnamed: C1.1, LED1.A, R1.1, U1.4 (OUT), U$1.P$1, U$1.P$2, U$1.P$3

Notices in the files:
parts and their libraries:
SparkFun-Resistors: Licensing: CC v3.0 Share-Alike You are welcome to use this library for commercial purposes.
